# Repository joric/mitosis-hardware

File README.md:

Kicad Mitosis
=============

A port of original Mitosis converted with [altium2kicad](https://github.com/thesourcerer8/altium2kicad).

Disclaimer
----------

* hanya - files taken from [here](https://github.com/hanya/mitosis-hardware/tree/kicad) (with a working net), this is the most accurate
* default - cleaned up autoconverted version, should be ready for export
* big-pads - wider pads for YJ-14015 (still a bit unfinished check pads carefully!)
* autoconverted - raw autoconverted board (misplaced labels, messed up outlines, etc.)
* interphase - KiCad files taken from [here](https://github.com/Durburz/interphase) (Mitosis with a little bit more keys), see [reddit][interphase]
* orthrus - KiCad files taken from [here](https://github.com/bezmi/orthrus) (great Atreus62/Mitosis crossover by bezmi), see [reddit][orthrus]

Converting
----------

Apply .pl scripts then delete all unnecessary Edge.Cuts (such as 10x10 cm outline).

Remove board outline from Dwgs.User.

All footprint texts made invisible ("Switch", "NRF51822", etc. - they weren't in the gerbers).

Battery footprint and mitosis branding will appear misplaced, so move them down.

Check results in 3D viewer against the original gerber.

Editing
-------

To make bigger nrf51 pads, use select - Edit All Pads, set width to 2.5 mm and apply for all.

Exporting
---------

Use File-Plot command to export gerber files.

Check F.Cu, B.Cu, B.Paste, F.Paste, B.Silk, F.Silk and the Edge.Cuts layers, and also Dwgs.User.

Do not check Exclude PCB edge layer from other layers.

Then export Drill file, use Gerber in the Format section and check Minimal header.

References
----------

* [Acrylic case friendly mod (Altium)](https://github.com/YCF/mitosis-hardware-mod)
* [Hanya's port with a working net (KiCad)](https://github.com/hanya/mitosis-hardware)
* [A mod with battery between the switches (video)](https://www.reddit.com/r/MechanicalKeyboards/comments/6tcctx/new_buildmitosisplusthank_you_reverse_bias/dlk3rg7/)
* [Interphase mod with more keys](https://github.com/Durburz/interphase)
* [Orthrus - wireless split, 56 keys, based on Mitosis and Atreus](https://github.com/bezmi/orthrus)

[orthrus]: https://www.reddit.com/r/MechanicalKeyboards/comments/8txry7/orthrus_wireless_split_56_keys_based_on_mitosis
[interphase]: https://www.reddit.com/r/MechanicalKeyboards/comments/7ggeww/photos_interphase_finished_my_prototype/

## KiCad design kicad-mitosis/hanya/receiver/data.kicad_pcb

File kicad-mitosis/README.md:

Kicad Mitosis
=============

A port of original Mitosis converted with [altium2kicad](https://github.com/thesourcerer8/altium2kicad).

Disclaimer
----------

NEITHER OF THOSE LAYOUTS WERE ACTUALLY CHECKED IN PRODUCTION, USE AT YOUR OWN RISK!

* default - cleaned up autoconverted version, should be ready for export
* YJ-14015-support - wider pads for YJ-14015 (still a bit unfinished check pads carefully!)
* autoconverted - raw autoconverted board (misplaced labels, messed up outlines, etc.)

Mind that there's no network yet so it couldn't be autorouted.

Converting
----------

Apply .pl scripts then delete all unnecessary Edge.Cuts (such as 10x10 cm outline).

Remove board outline from Dwgs.User.

All footprint texts made invisible ("Switch", "NRF51822", etc. - they weren't in the gerbers).

Battery footprint and mitosis branding will appear misplaced, so move them down.

Check results in 3D viewer against the original gerber.

Editing
-------

To make bigger nrf51 pads, use select - Edit All Pads, set width to 2.5 mm and apply for all.

Exporting
---------

Use File-Plot command to export gerber files.

Check F.Cu, B.Cu, B.Paste, F.Paste, B.Silk, F.Silk and the Edge.Cuts layers, and also Dwgs.User.

Do not check Exclude PCB edge layer from other layers.

Then export Drill file, use Gerber in the Format section and check Minimal header.

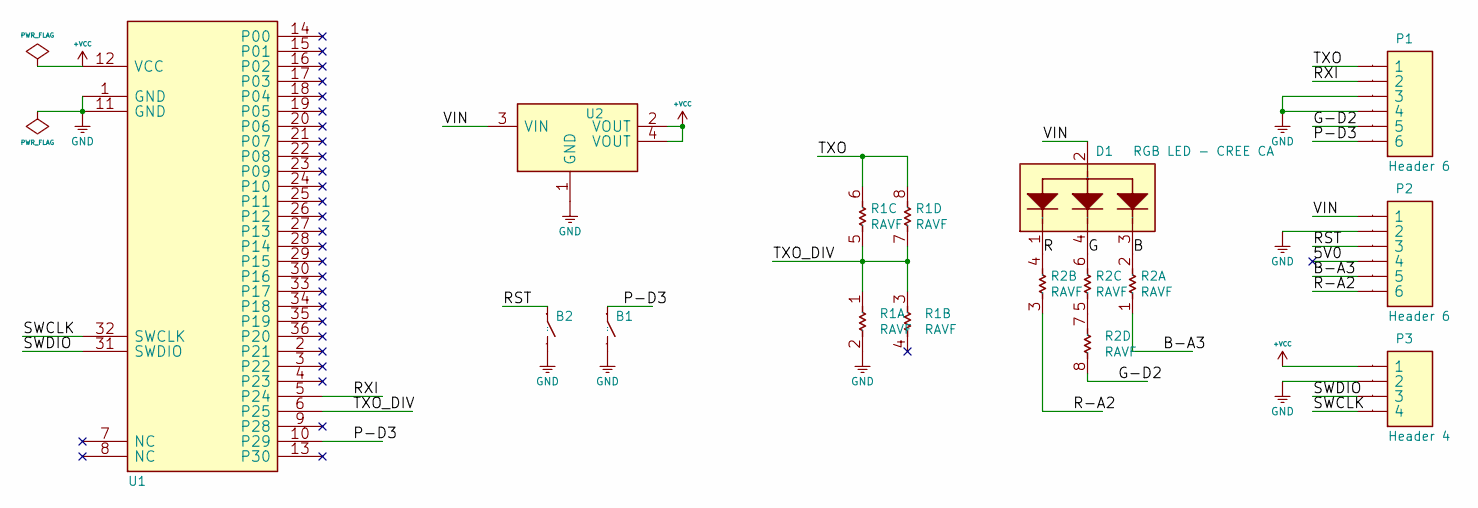
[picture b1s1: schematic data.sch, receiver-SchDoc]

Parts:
B1, B2: TACTILE_BUTTON
D1: RGB LED - CREE CA; PLCC4-RGBLED
P1, P2: Header 6; HDR1X6
P3: Header 4; HDR1X4
R1, R2: RAVF; 1206_quad_res
U1: Core51822B
U2: SOT230P700X180-4N

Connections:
/5V0: P2.4
/B: D1.3 (B), R2.2
/B-A3: P2.5, R2.1
/G: D1.4 (G), R2.6 (2)
/G-D2: P1.5, R2.8 (2)
/P-D3: B1.1, P1.6, U1.10 (P29)
/R: D1.1 (R), R2.4 (2)
/R-A2: P2.6, R2.3 (1)
/RST: B2.1, P2.3
/RXI: P1.2, U1.5 (P24)
/SWCLK: P3.4, U1.32 (SWCLK)
/SWDIO: P3.3, U1.31 (SWDIO)
/TXO: P1.1, R1.6 (2), R1.8 (2)
/TXO_DIV: R1.1, R1.3 (1), R1.5 (1), R1.7 (1), U1.6 (P25)
/VIN: D1.2 (CA), P2.1, U2.3 (VIN)
GND: B1.2, B2.2, P1.3, P1.4, P2.2, P3.2, R1.2, U1.1 (GND), U1.11 (GND), U2.1 (GND)
unnamed: R2.5 (1), R2.7 (1)
VCC: P3.1, U1.12 (VCC), U2.2 (VOUT), U2.4 (VOUT)

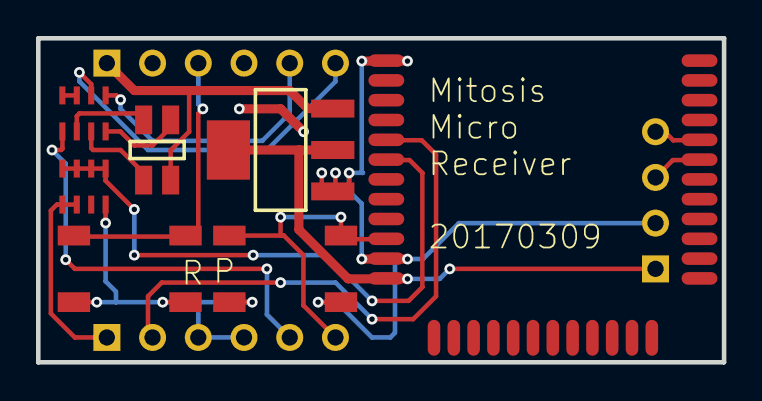
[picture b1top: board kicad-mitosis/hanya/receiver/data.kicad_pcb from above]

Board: 2 copper layers, 38.1 x 18.0 mm, 10 parts (1 on the bottom side), 17 nets.

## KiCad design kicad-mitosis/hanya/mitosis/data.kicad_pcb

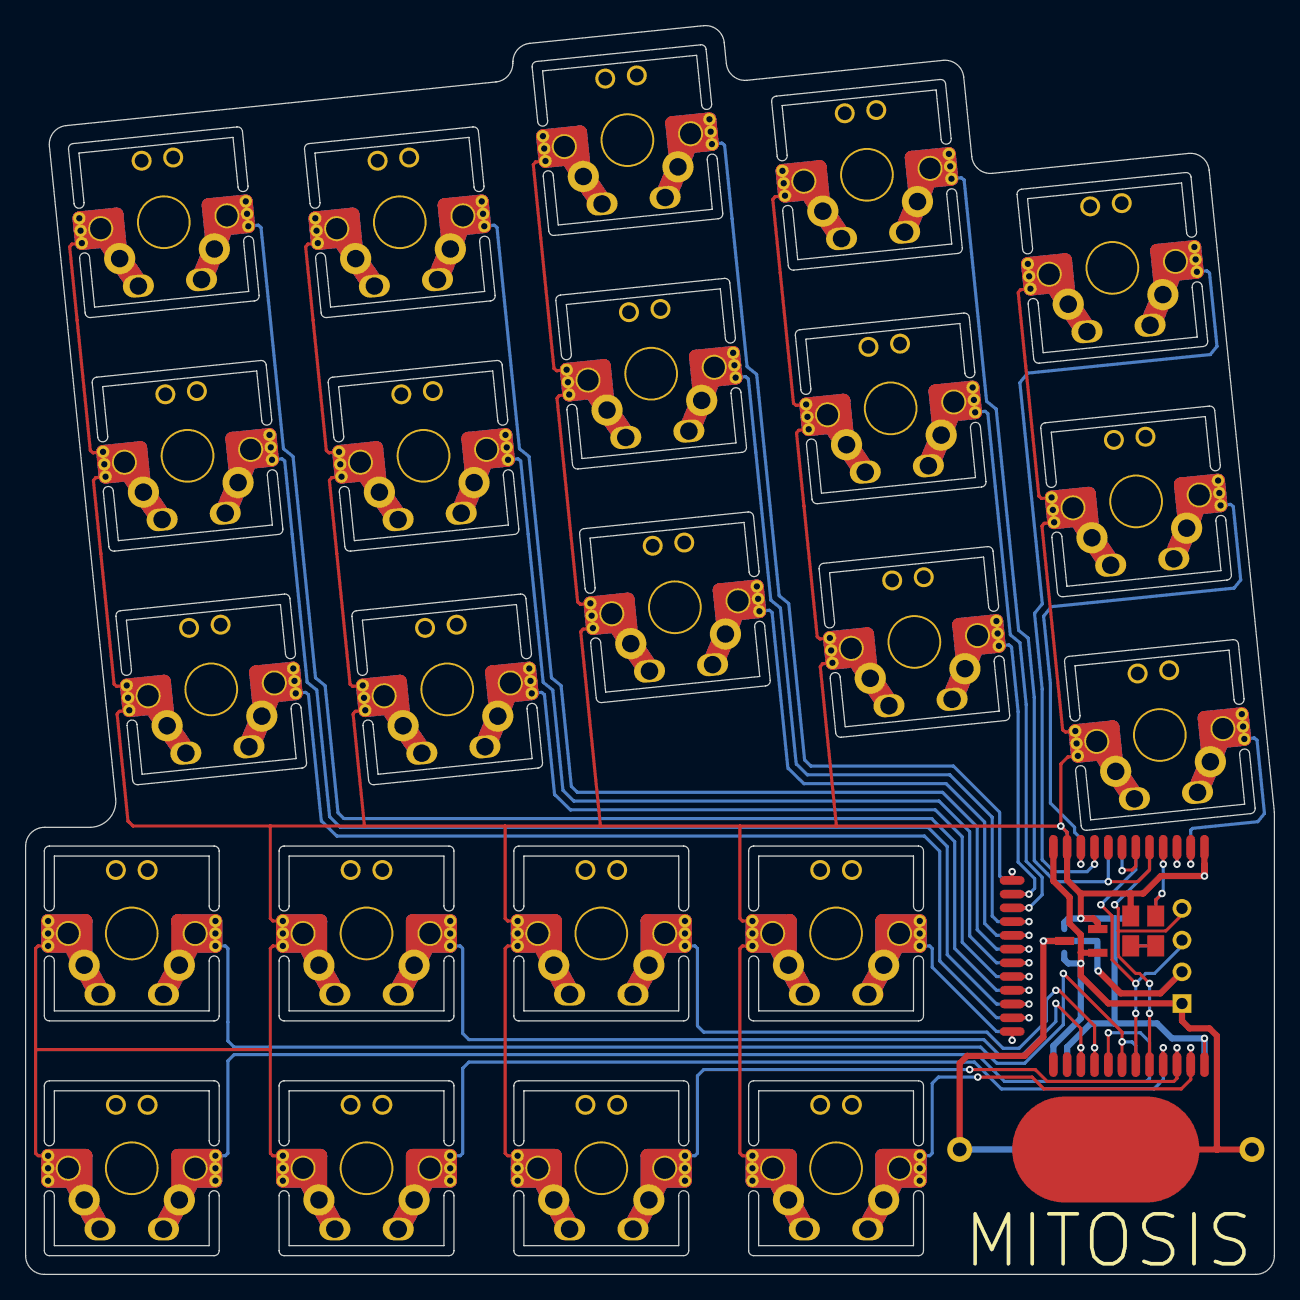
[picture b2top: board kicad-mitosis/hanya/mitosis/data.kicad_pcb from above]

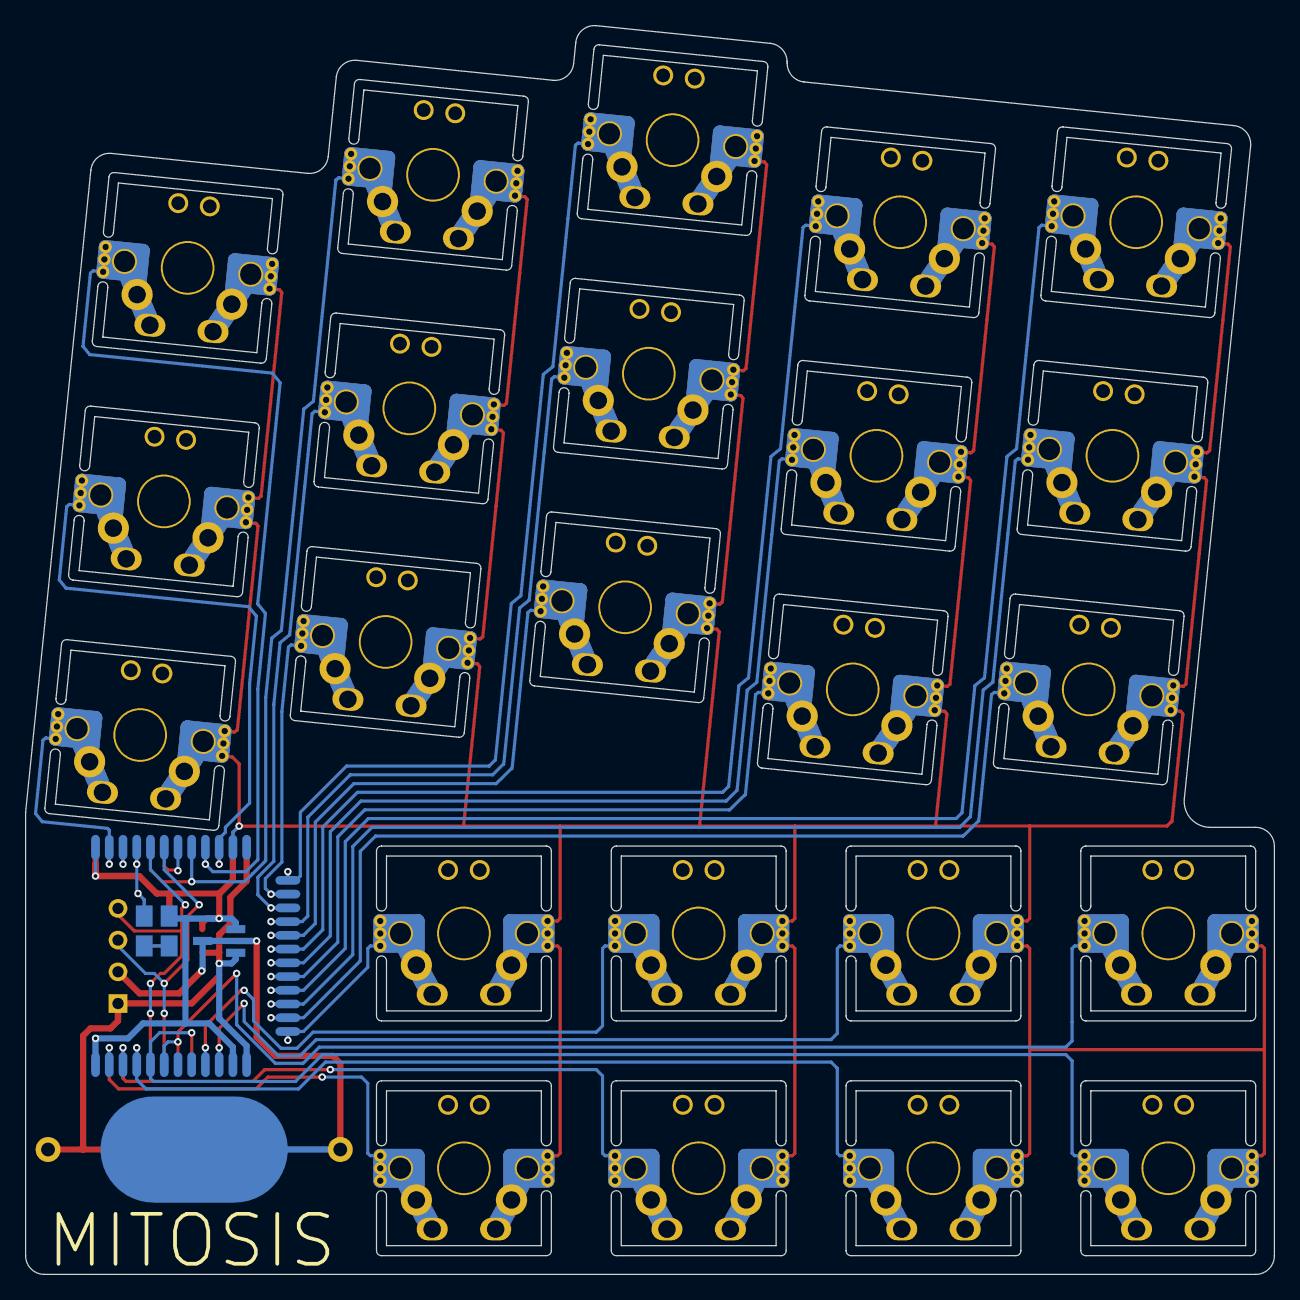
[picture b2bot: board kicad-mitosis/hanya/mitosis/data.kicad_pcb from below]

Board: 2 copper layers, 100.0 x 100.0 mm, 33 parts (4 on the bottom side), 33 nets.

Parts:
D1, D2: 0603; RESC2012X06N
E1: Battery; CR2032_pad
P1: Header_4; HDR1X4
Q1, Q2: SI2302; SOT-23
R1, R2: 0603; RESC2012X06N
S1, S2, S3, S4, S5, S6, S7, S8, S9, S10, S11, S12, S13, S14, S15: CHERRY MX; cherry_angled
S16, S17, S18, S19, S20, S21, S22, S23: CHERRY MX; cherry
U1, U2: Core51822B

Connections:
/GND_P: E1.2, P1.2, Q1.3, Q2.3
/L1: D1.1, R1.2
/L2: D2.1, R2.2
/LED: D1.2, D2.2, U1.4, U2.33
/S1: S1.2, S1.4, S1.6, S1.8, S1.10, S1.12, U1.21, U2.16
/S2: S2.2, S2.4, S2.6, S2.8, S2.10, S2.12, U1.18, U2.19
/S3: S3.2, S3.4, S3.6, S3.8, S3.10, S3.12, U1.13, U2.24
/S4: S4.2, S4.4, S4.6, S4.8, S4.10, S4.12, U1.5, U2.29
/S5: S5.2, S5.4, S5.6, S5.8, S5.10, S5.12, U1.9, U2.28
/S6: S6.2, S6.4, S6.6, S6.8, S6.10, S6.12, U1.22, U2.15
/S7: S7.2, S7.4, S7.6, S7.8, S7.10, S7.12, U1.19, U2.18
/S8: S8.2, S8.4, S8.6, S8.8, S8.10, S8.12, U1.16, U2.21
/S9: S9.2, S9.4, S9.6, S9.8, S9.10, S9.12, U1.15, U2.22
/S10: S10.2, S10.4, S10.6, S10.8, S10.10, S10.12, U1.10, U2.27
/S11: S11.2, S11.4, S11.6, S11.8, S11.10, S11.12, U1.23, U2.14
/S12: S12.2, S12.4, S12.6, S12.8, S12.10, S12.12, U1.20, U2.17
/S13: S13.2, S13.4, S13.6, S13.8, S13.10, S13.12, U1.17, U2.20
/S14: S14.2, S14.4, S14.6, S14.8, S14.10, S14.12, U1.14, U2.23
/S15: S15.2, S15.4, S15.6, S15.8, S15.10, S15.12, U1.2, U2.35
/S16: S16.2, S16.4, S16.6, S16.8, S16.10, S16.12, U1.30, U2.6
/S17: S17.2, S17.4, S17.6, S17.8, S17.10, S17.12, U1.27, U2.10
/S18: S18.2, S18.4, S18.6, S18.8, S18.10, S18.12, U1.28, U2.9
/S19: S19.2, S19.4, S19.6, S19.8, S19.10, S19.12, U1.24, U2.13
/S20: S20.2, S20.4, S20.6, S20.8, S20.10, S20.12, U1.29, U2.5
/S21: S21.2, S21.4, S21.6, S21.8, S21.10, S21.12, U1.33, U2.4
/S22: S22.2, S22.4, S22.6, S22.8, S22.10, S22.12, U1.34, U2.3
/S23: S23.2, S23.4, S23.6, S23.8, S23.10, S23.12, U1.35, U2.2
/SWCLK: P1.4, U1.32, U2.32
/SWDIO: P1.3, U1.31, U2.31
/W23: U1.3, U2.34
/W26: U1.6, U2.30
GND: Q1.2, Q2.2, R1.1, R2.1, S1.1, S1.3, S1.5, S1.7, S1.9, S1.11, S2.1, S2.3, S2.5, S2.7, S2.9, S2.11, S3.1, S3.3, S3.5, S3.7, S3.9, S3.11, S4.1, S4.3, S4.5, S4.7, S4.9, S4.11, S5.1, S5.3, S5.5, S5.7, S5.9, S5.11, S6.1, S6.3, S6.5, S6.7, S6.9, S6.11, S7.1, S7.3, S7.5, S7.7, S7.9, S7.11, S8.1, S8.3, S8.5, S8.7, S8.9, S8.11, S9.1, S9.3, S9.5, S9.7, S9.9, S9.11, S10.1, S10.3, S10.5, S10.7, S10.9, S10.11, S11.1, S11.3, S11.5, S11.7, S11.9, S11.11, S12.1, S12.3, S12.5, S12.7, S12.9, S12.11, S13.1, S13.3, S13.5, S13.7, S13.9, S13.11, S14.1, S14.3, S14.5, S14.7, S14.9, S14.11, S15.1, S15.3, S15.5, S15.7, S15.9, S15.11, S16.1, S16.3, S16.5, S16.7, S16.9, S16.11, S17.1, S17.3, S17.5, S17.7, S17.9, S17.11, S18.1, S18.3, S18.5, S18.7, S18.9, S18.11, S19.1, S19.3, S19.5, S19.7, S19.9, S19.11, S20.1, S20.3, S20.5, S20.7, S20.9, S20.11, S21.1, S21.3, S21.5, S21.7, S21.9, S21.11, S22.1, S22.3, S22.5, S22.7, S22.9, S22.11, S23.1, S23.3, S23.5, S23.7, S23.9, S23.11, U1.1, U1.11, U1.36, U2.1, U2.11, U2.26, U2.36
VCC: E1.1, P1.1, Q1.1, Q2.1, U1.12, U2.12

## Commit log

2017-09-29 added kicad-mitosis
2017-09-30 cleaned-up renamed to default
2017-09-30 updated files
2017-09-30 added default gerbers
2017-10-10 added reference links
2017-10-10 added interphase mod
2017-10-10 renamed to big-pads
2018-06-27 started iris outline
2018-07-09 updated readme, added link to Orthus
2018-07-10 added orthrus
2018-11-14 added mitosis-laser.dxf
2018-11-16 updated mitosis-laser.dxf (reexported with qcad dxf r14)
